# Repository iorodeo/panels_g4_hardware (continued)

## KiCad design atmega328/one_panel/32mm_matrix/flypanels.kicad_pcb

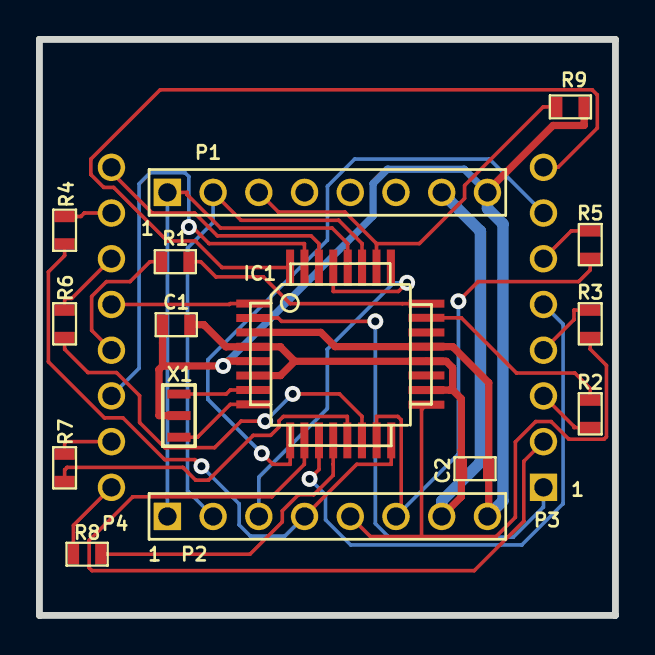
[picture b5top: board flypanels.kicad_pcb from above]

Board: 2 copper layers, 32.0 x 32.0 mm, 16 parts (0 on the bottom side), 32 nets.

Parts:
C1, C2: 0.1uF; SM0603
IC1: ATMEGA328-A; TQFP32
MATRIX1: LED_8X8; LED_8x8
P1, P2: CONN_8; CONN_8x1
R1, R2, R3, R4, R5, R6, R7, R8: 150; SM0603
R9: 10K; SM0603
X1: CER_RESO; XZL_CR

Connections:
GND: C1.2, C2.2, IC1.3, IC1.5, IC1.21, P1.8, P2.8, R9.2, X1.2
unnamed: IC1.29, P2.3
unnamed: IC1.31, MATRIX1.14
unnamed: IC1.11, MATRIX1.5
unnamed: MATRIX1.4, R3.1
unnamed: MATRIX1.10, R4.1
unnamed: MATRIX1.3, R2.1
unnamed: MATRIX1.6, R5.1
unnamed: MATRIX1.15, R7.1
unnamed: IC1.16, P2.4, R4.2
unnamed: IC1.15, P2.6, R5.2
unnamed: IC1.8, X1.3
unnamed: IC1.30, MATRIX1.9
unnamed: IC1.24, R1.2
unnamed: IC1.23, R2.2
unnamed: IC1.14, R6.2
unnamed: IC1.12, R8.2
unnamed: IC1.13, R7.2
unnamed: IC1.32, MATRIX1.8
unnamed: IC1.2, MATRIX1.1
unnamed: IC1.10, MATRIX1.2
unnamed: MATRIX1.13, R1.1
unnamed: IC1.28, P1.1, P2.1
unnamed: IC1.7, X1.1
unnamed: IC1.9, MATRIX1.7
unnamed: IC1.1, MATRIX1.12
unnamed: IC1.27, P1.2, P2.2
unnamed: IC1.17, P2.5, R3.2
unnamed: MATRIX1.16, R8.1
unnamed: MATRIX1.11, R6.1
unnamed: IC1.26, P1.3, R9.1
VCC: C1.1, C2.1, IC1.4, IC1.6, IC1.18, IC1.20, P1.7, P2.7
